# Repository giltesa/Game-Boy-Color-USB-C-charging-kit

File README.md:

# Game Boy Color USB-C Charging Kit

The **Game Boy Color USB-C Charging Kit** is a circuit that allows you to charge a **Nintendo Game Boy Color** by **USB-C** and use a **Li-ion** battery instead of AA batteries.

This circuit includes the famous **TP4056** and **DW01A**. The first one is the device in charge of charging the battery, and the second one is protecting the lifetime of the battery of the over-discharge.

This kit includes two boards. If you want to install it easy, it's enough with the main board which doesn't need any cable for working. However, if you want to have the status LEDs in the same place as the original status LED, then you will need to solder the second board and joint both with 3 cables. You can choose the best option for you.

This is the maind board:

And this one is the LED board:

## Youtube:

Game Boy Color USB-C Charging Kit (Installation)

A small demostration about how this works:

*(red light = charging, green light = finish to charge, white = GBC is power on)*

Battery test: 1500 mAh = 8h 40m

## Would you like it?

https://shop.giltesa.com/product/game-boy-color-usb-c-charging-kit/

## More

- [giltesa.com](https://giltesa.com "giltesa.com")
- [twitter.com](https://twitter.com/giltesa "twitter.com")

## License

This project is licensed under a **Creative Commons** license:
**[Attribution-NonCommercial-ShareAlike 4.0 International (CC BY-NC-SA 4.0) ](https://creativecommons.org/licenses/by-nc-sa/4.0/)**

Check the [LICENSE.md](LICENSE.md) for more information.

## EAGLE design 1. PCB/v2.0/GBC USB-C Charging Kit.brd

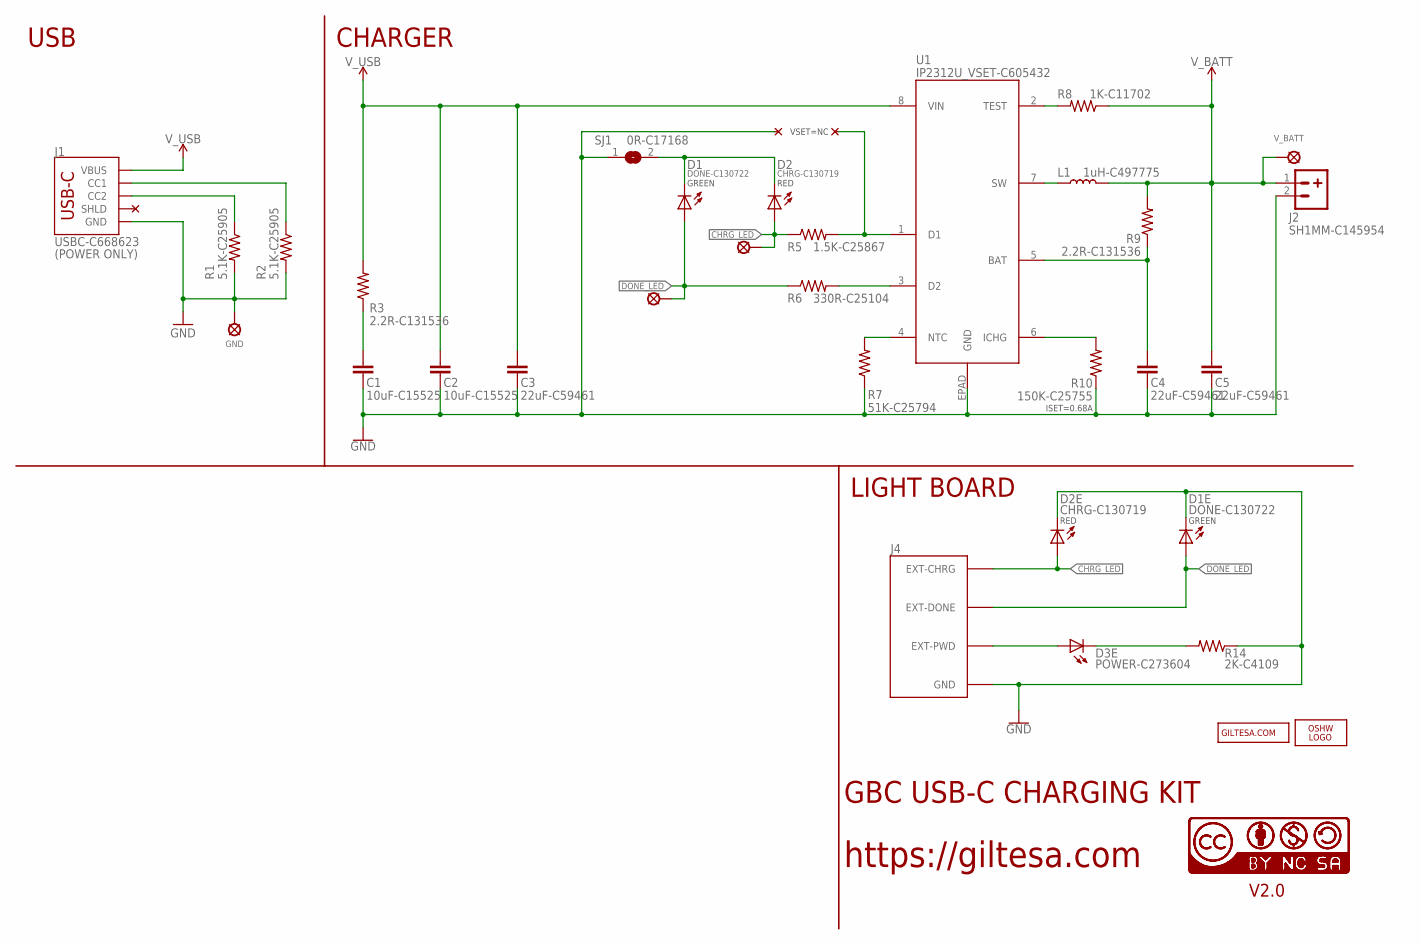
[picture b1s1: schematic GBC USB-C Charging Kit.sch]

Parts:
C1, C2: 10uF-C15525; C0402_S
C3, C4, C5: 22uF-C59461; C0603_S
D1, D1E: DONE-C130722; L0402
D2, D2E: CHRG-C130719; L0402
D3E: POWER-C273604; L0402
J1: USBC-C668623; USB-C_6P
J2: SH1MM-C145954; JST-2-1MM-SMD_RIGHT
J4: GBC_LED_V2
L1: 1uH-C497775; PSPMAA0402
LOGO2: OSHW_LOGO_FILLX0150-NT; OSHW_FILLX150_NOTEXT
R1, R2: 5.1K-C25905; R0402
R3, R9: 2.2R-C131536; R0402
R5: 1.5K-C25867; R0402
R6: 330R-C25104; R0402
R7: 51K-C25794; R0402
R8: 1K-C11702; R0402
R10: 150K-C25755; R0402
R14: 2K-C4109; R0402
SJ1: 0R-C17168; JUMPER-SMD_0402
U1: IP2312U_VSET-C605432; IP2312
U$1: V_BATT; PAD_1.25
U$2: GND; PAD_1.25
U$6: CC-BY-NC-SA15MM; CC-BY-NC-SA_15MM
U$16: GILTESA.COM_MASK; GILTESA.COM_MASK_15MM
U$17: CC-NC-BCNIX; CC-NC-B_NIX
U$24: CHRG_LED; SOLDER_PAD_1.3
U$25: DONE_LED; SOLDER_PAD_1.3

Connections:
CHRG_LED: D2.A, D2E.A, J4.EXT-CHRG, R5.1, U$24.P$1
DONE_LED: D1.A, D1E.A, J4.EXT-DONE, R6.1, U$25.P$1
GND: C1.1, C2.1, C3.1, C4.1, C5.1, D1E.C, D2E.C, J1.A12-GND (GND), J1.B12-GND (GND), J2.2, J4.GND, R1.2, R2.2, R7.1, R10.1, R14.1, SJ1.1, U1.EPAD (GND), U$2.P$1
unnamed: D1.C, D2.C, SJ1.2
unnamed: J1.B5 (CC2), R1.1
unnamed: R8.2, U1.2 (TEST)
unnamed: D3E.A, J4.EXT-PWD
unnamed: D3E.C, R14.2
unnamed: J1.A5 (CC1), R2.1
unnamed: C4.2, R9.1, U1.5 (BAT)
unnamed: C1.2, R3.1
unnamed: R5.2, U1.1 (D1)
unnamed: R7.2, U1.4 (NTC)
unnamed: R10.2, U1.6 (ICHG)
unnamed: R6.2, U1.3 (D2)
unnamed: L1.P$1 (1), U1.7 (SW)
V_BATT: C5.2, J2.1, L1.P$2 (2), R8.1, R9.2, U$1.P$1
V_USB: C2.2, C3.2, J1.A9-VBUS (VBUS), J1.B9-VBUS (VBUS), R3.2, U1.8 (VIN)

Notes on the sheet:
GBC USB-C CHARGING KIT
https://giltesa.com
V2.0
(POWER ONLY)
USB
CHARGER
LIGHT BOARD
ISET=0.68A
GREEN
RED
VSET=NC

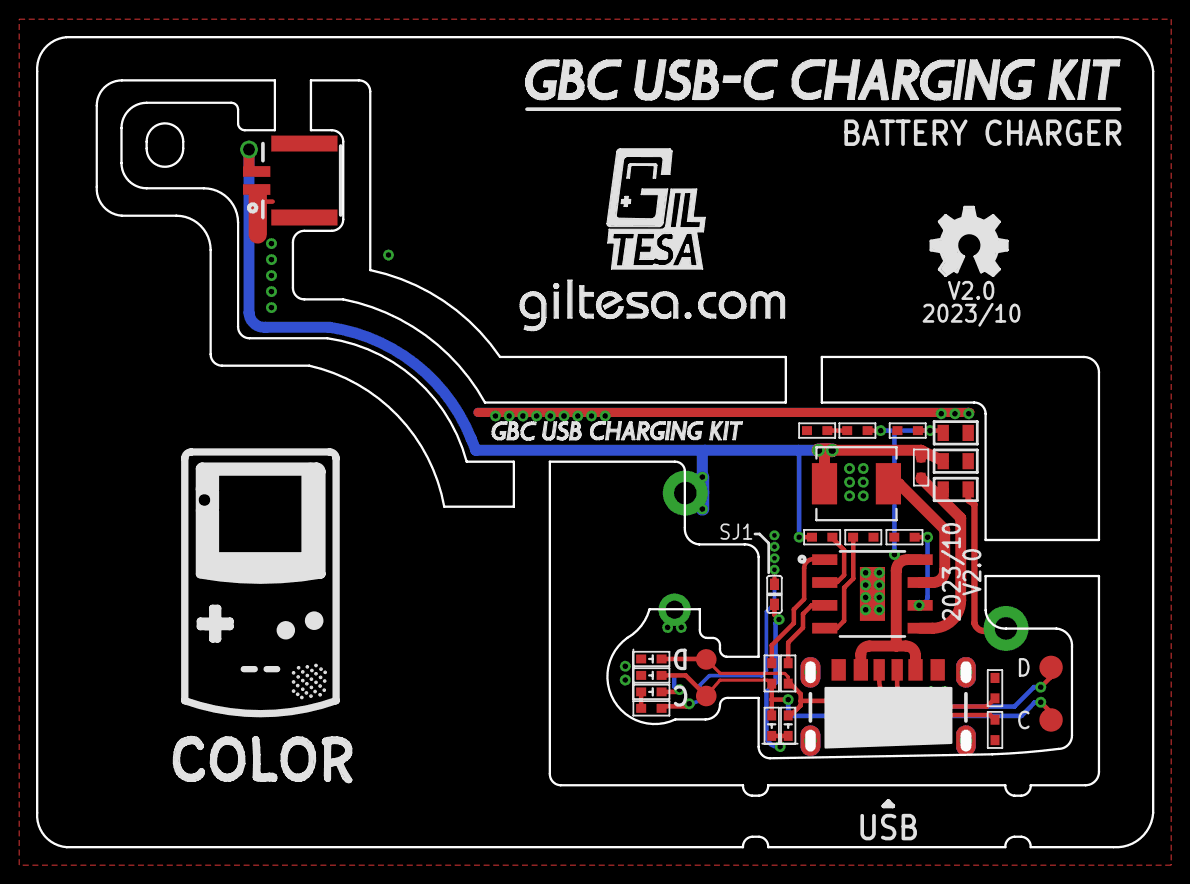
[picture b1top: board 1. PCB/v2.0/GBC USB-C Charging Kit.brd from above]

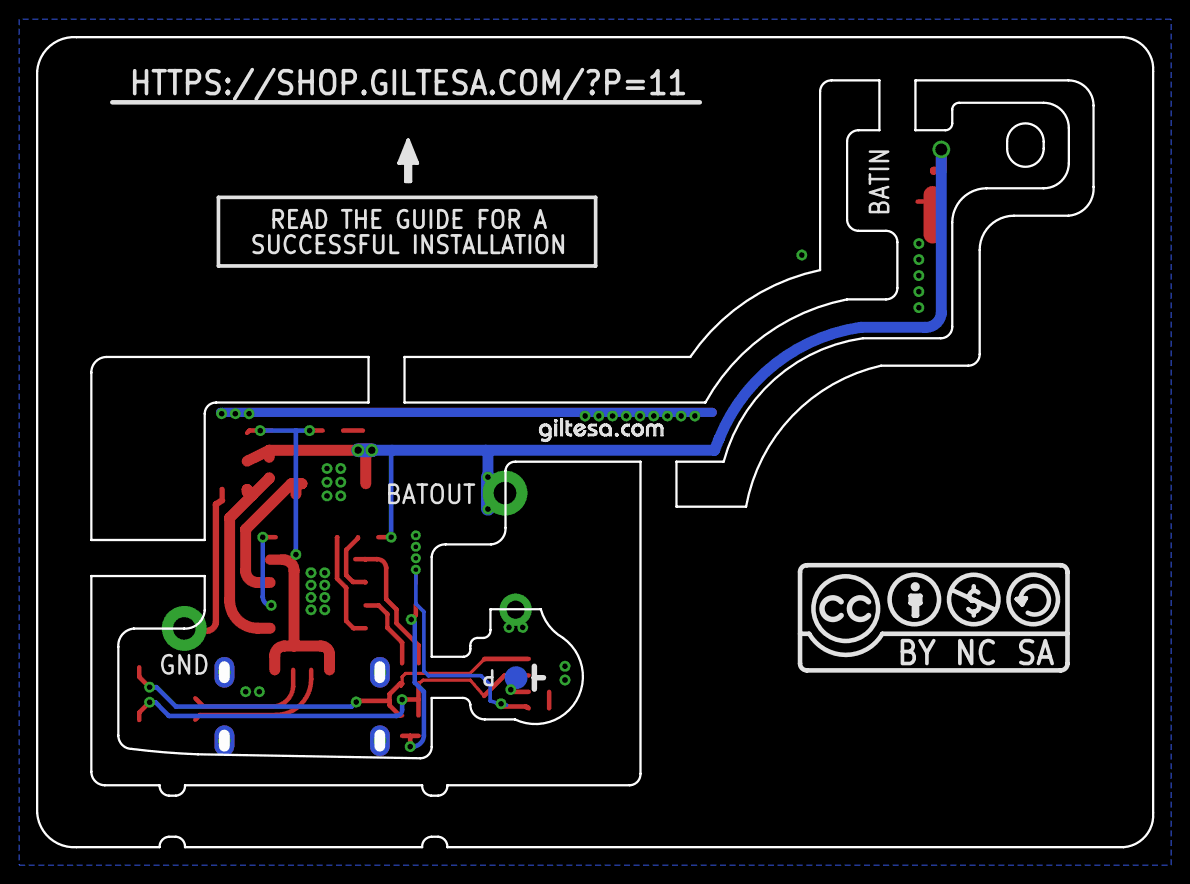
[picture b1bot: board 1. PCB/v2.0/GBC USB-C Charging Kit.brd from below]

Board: 2 copper layers, 62.0 x 45.0 mm, 39 parts (2 on the bottom side), 18 nets.

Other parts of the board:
U$3: GBC_FRAME
U$8: GBC_FRAME_LOGO
U$14: GAME_BOY_COLOR_USB_CHARGING_KIT_NON
U$18: GILTESA_LOGO_MASK_7MM
U$28: GILTESA.COM_MASK_7MM@1

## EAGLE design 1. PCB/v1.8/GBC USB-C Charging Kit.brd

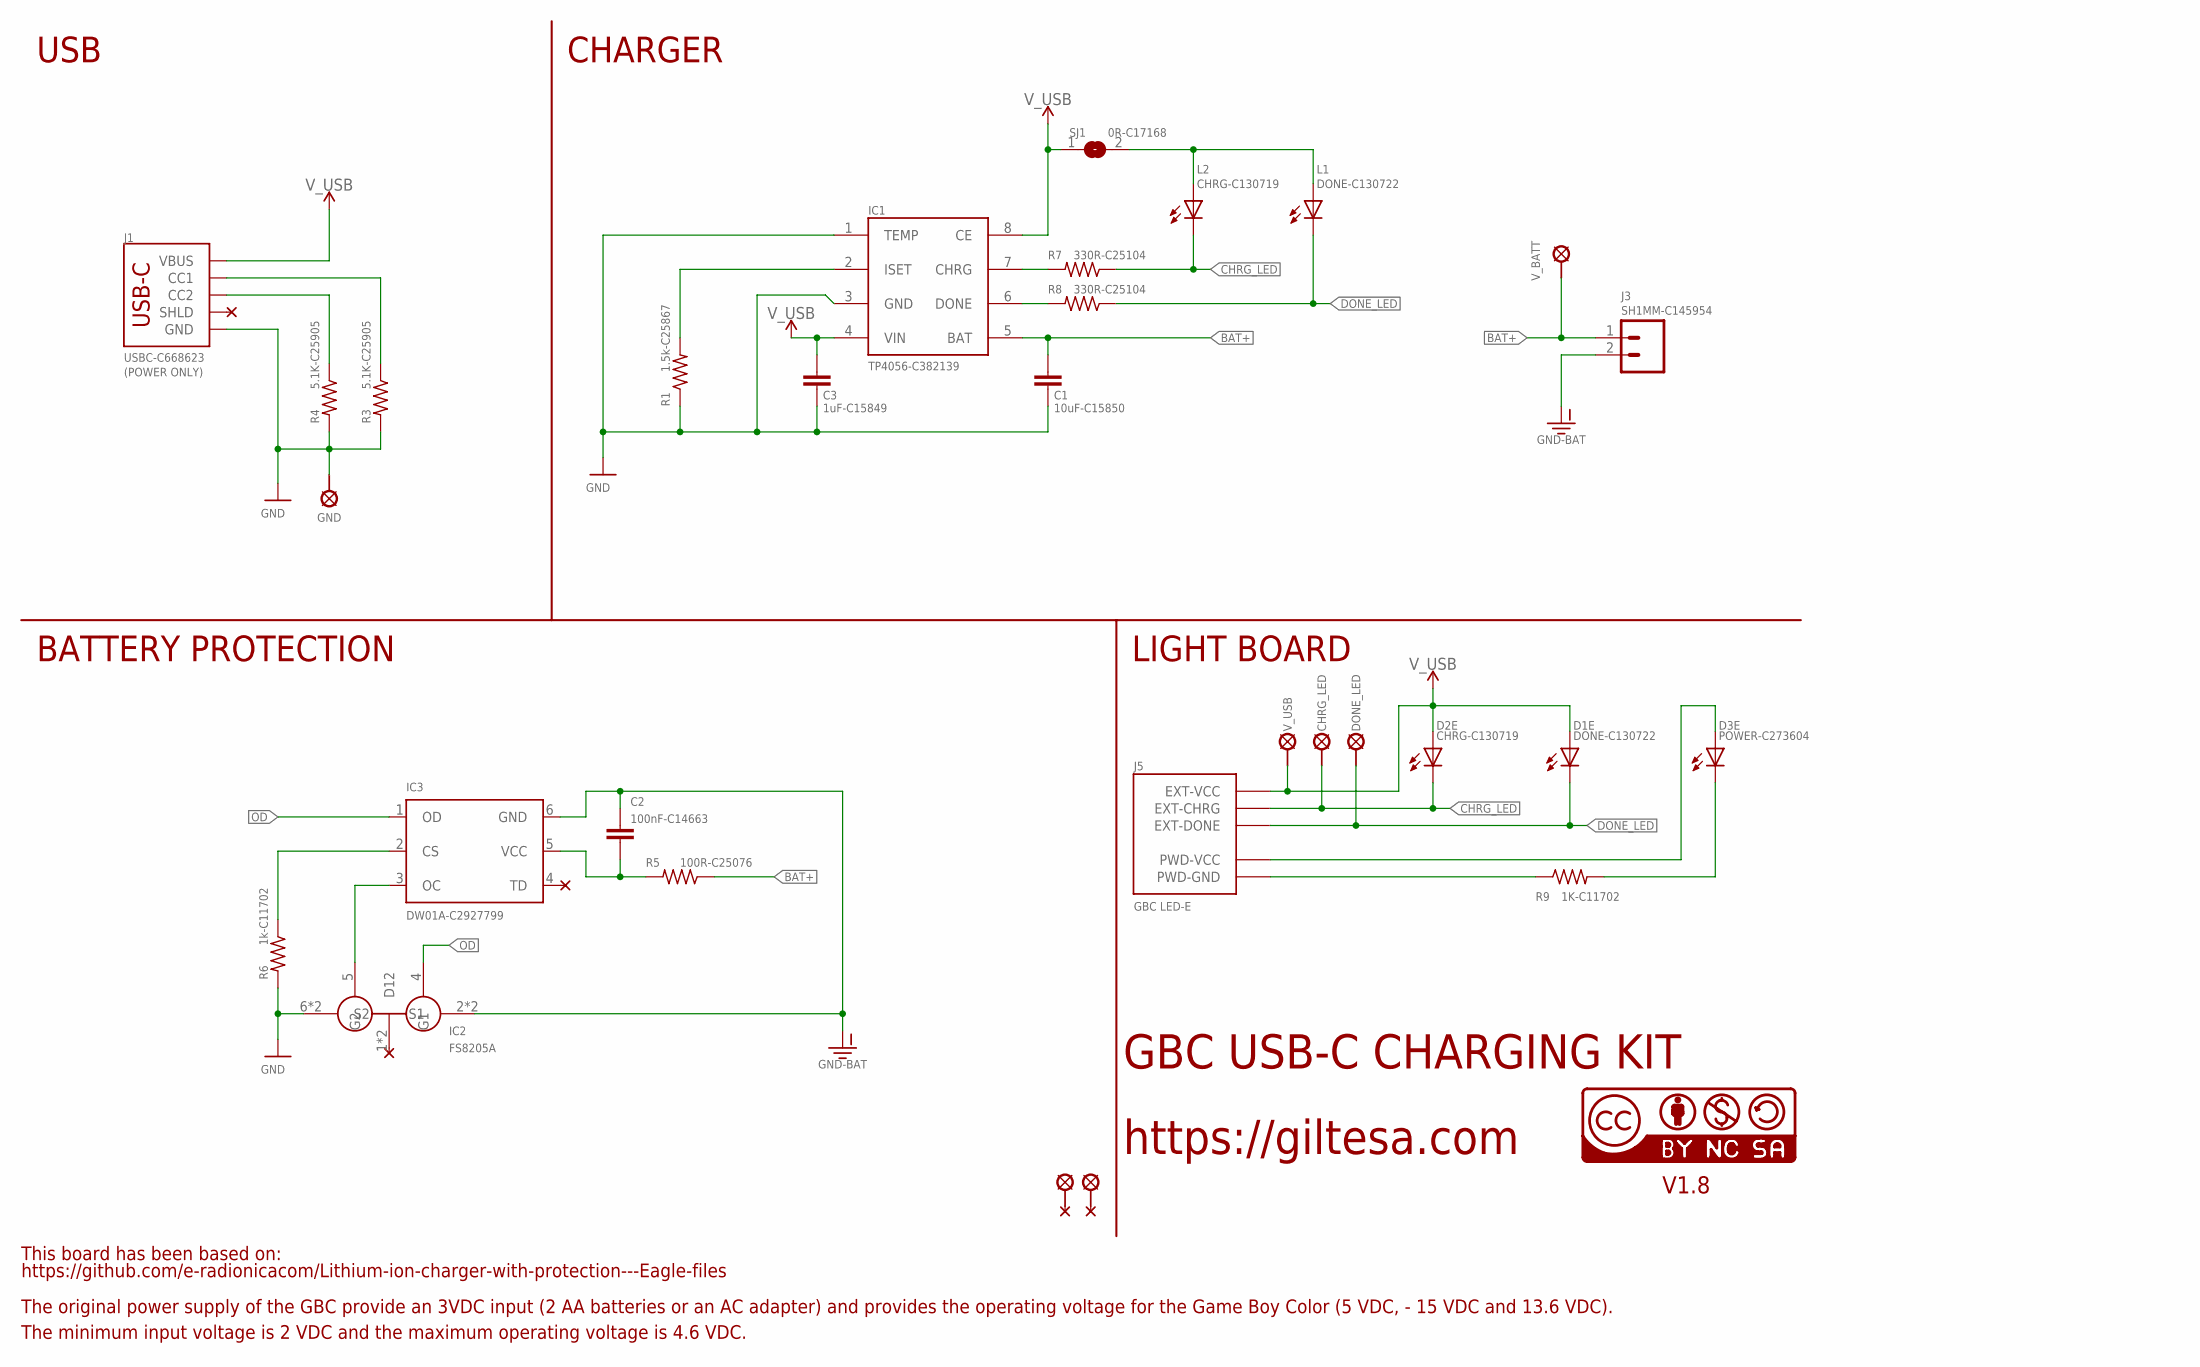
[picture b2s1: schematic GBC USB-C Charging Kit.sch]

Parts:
C1: 10uF-C15850; C0805_S
C2: 100nF-C14663; C0603_S
C3: 1uF-C15849; C0603_S
D1E: DONE-C130722; L0402
D2E: CHRG-C130719; L0402
D3E: POWER-C273604; L0402
IC1: TP4056-C382139; SOIC-8
IC2: 8205A-C2929075; TSSOP8
IC3: DW01A-C2927799; SOT23-6L
J1: USBC-C668623; USB-C_6P
J3: SH1MM-C145954; JST-2-1MM-SMD_RIGHT
J5: GBC LED-E; GBC_LED
L1: DONE-C130722; L0402
L2: CHRG-C130719; L0402
R1: 1.5k-C25867; R0402
R3, R4: 5.1K-C25905; R0402
R5: 100R-C25076; R0402
R6: 1k-C11702; R0402
R7, R8: 330R-C25104; R0402
R9: 1K-C11702; R0402
SJ1: 0R-C17168; JUMPER-SMD_0402
U$2: GND; PAD_1.25
U$17: CC-NC-BCNIX; CC-NC-B_NIX
U$18, U$32: SOLDER_PAD-2.5; SOLDER_PAD_2.5
U$24: CHRG_LED; SOLDER_PAD_1.3
U$25: DONE_LED; SOLDER_PAD_1.3
U$26: V_USB; SOLDER_PAD_1.3
U$29: V_BATT; PAD_1.25

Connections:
BAT+: C1.1, IC1.5 (BAT), J3.1, R5.1, U$29.P$1
CHRG: IC1.7 (CHRG), R7.2
CHRG_LED: D2E.C, J5.EXT-CHRG, L2.C, R7.1, U$24.P$1
DONE: IC1.6 (DONE), R8.2
DONE_LED: D1E.C, J5.EXT-DONE, L1.C, R8.1, U$25.P$1
GND: C1.2, C3.2, IC1.1 (TEMP), IC1.3 (GND), IC2.6 (S2), IC2.7 (S2), J1.GND1 (GND), J1.GND2 (GND), R1.1, R3.2, R4.2, R6.2, U$2.P$1
GND-BAT: C2.1, IC2.2 (S1), IC2.3 (S1), IC3.6 (GND), J3.2
ISET: IC1.2 (ISET), R1.2
unnamed: IC3.2 (CS), R6.1
unnamed: IC2.5 (G2), IC3.3 (OC)
unnamed: L1.A, L2.A, SJ1.2
unnamed: J1.B5 (CC2), R4.1
unnamed: D3E.A, J5.PWD-VCC
unnamed: D3E.C, R9.2
unnamed: J5.PWD-GND, R9.1
unnamed: J1.A5 (CC1), R3.1
OD: IC2.4 (G1), IC3.1 (OD)
VCC-DW: C2.2, IC3.5 (VCC), R5.2
V_USB: C3.1, D1E.A, D2E.A, IC1.4 (VIN), IC1.8 (CE), J1.VBUS1 (VBUS), J1.VBUS2 (VBUS), J5.EXT-VCC, SJ1.1, U$26.P$1

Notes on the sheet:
GBC USB-C CHARGING KIT
https://giltesa.com
V1.8
https://github.com/e-radionicacom/Lithium-ion-charger-with-protection---Eagle-files
This board has been based on:
(POWER ONLY)
IC2
FS8205A
The original power supply of the GBC provide an 3VDC input (2 AA batteries or an AC adapter) and provides the operating voltage for the Game Boy Color (5 VDC, - 15 VDC and 13.6 VDC).
The minimum input voltage is 2 VDC and the maximum operating voltage is 4.6 VDC.
USB
CHARGER
BATTERY PROTECTION
LIGHT BOARD

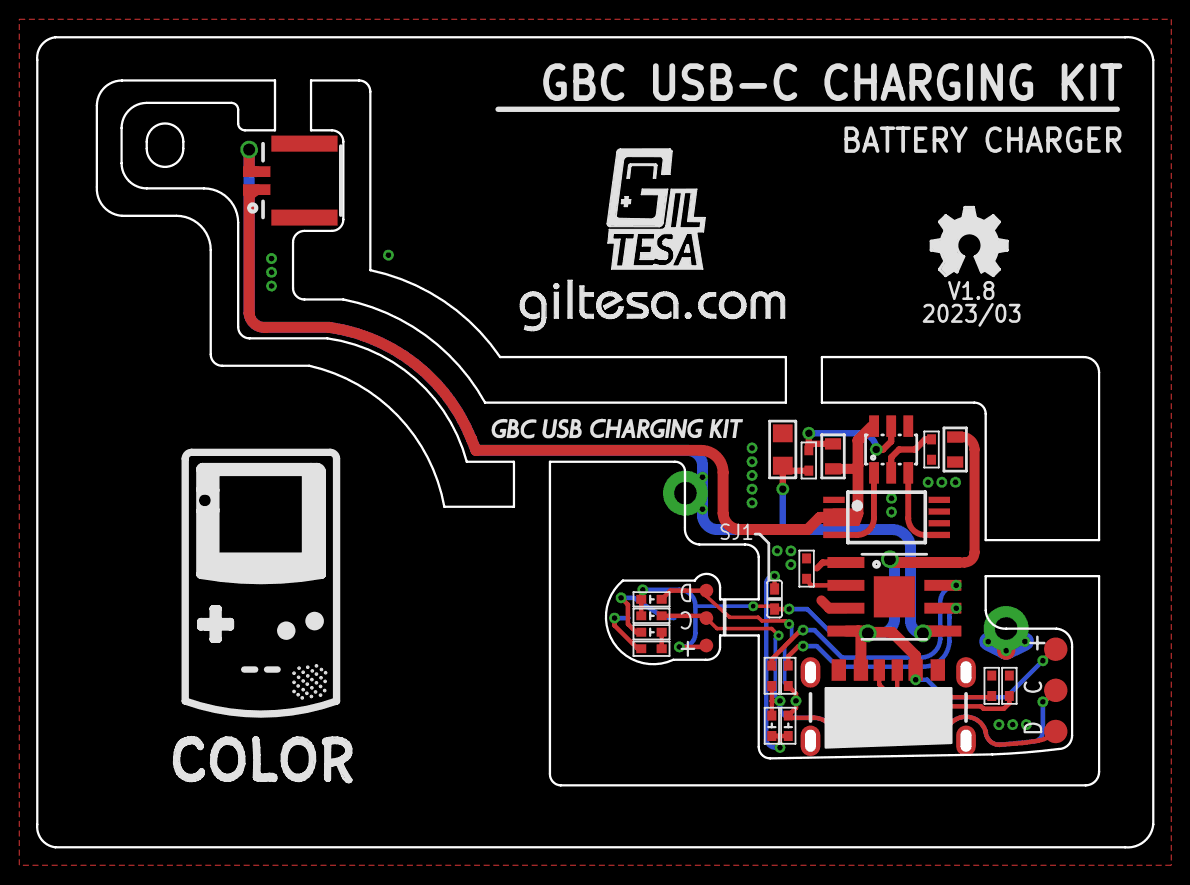
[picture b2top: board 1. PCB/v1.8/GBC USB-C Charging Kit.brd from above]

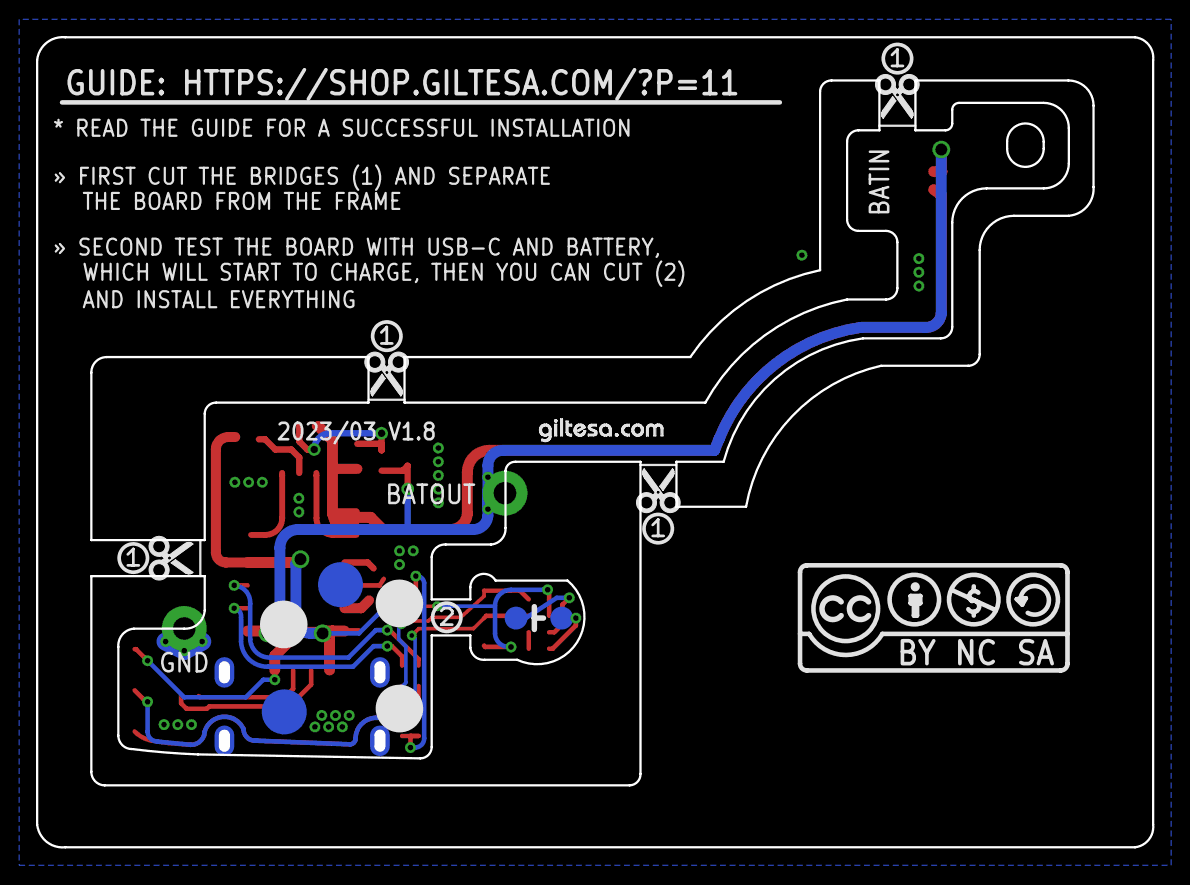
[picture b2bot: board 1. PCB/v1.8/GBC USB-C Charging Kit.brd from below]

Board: 2 copper layers, 62.0 x 45.0 mm, 48 parts (13 on the bottom side), 19 nets.

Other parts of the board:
LOGO3: OSHW_LOGO_FILLX0150-NT; OSHW_FILLX150_NOTEXT
U$4, U$8, U$11, U$13: SCISSOR_ONE
U$6, U$10, U$15, U$27: SCISSOR
U$7: CC-BY-NC-SA15MM; CC-BY-NC-SA_15MM
U$9: GAME_BOY_COLOR_USB_CHARGING_KIT_NON
U$12: GILTESA_LOGO_MASK_7MM
U$14: SCISSOR_TWO
U$20: GILTESA.COM_MASK
U$21: GAME_BOY_COLOR_1.2
U$23: GAME_BOY_COLOR_2
U$28: GILTESA.COM_MASK_7MM

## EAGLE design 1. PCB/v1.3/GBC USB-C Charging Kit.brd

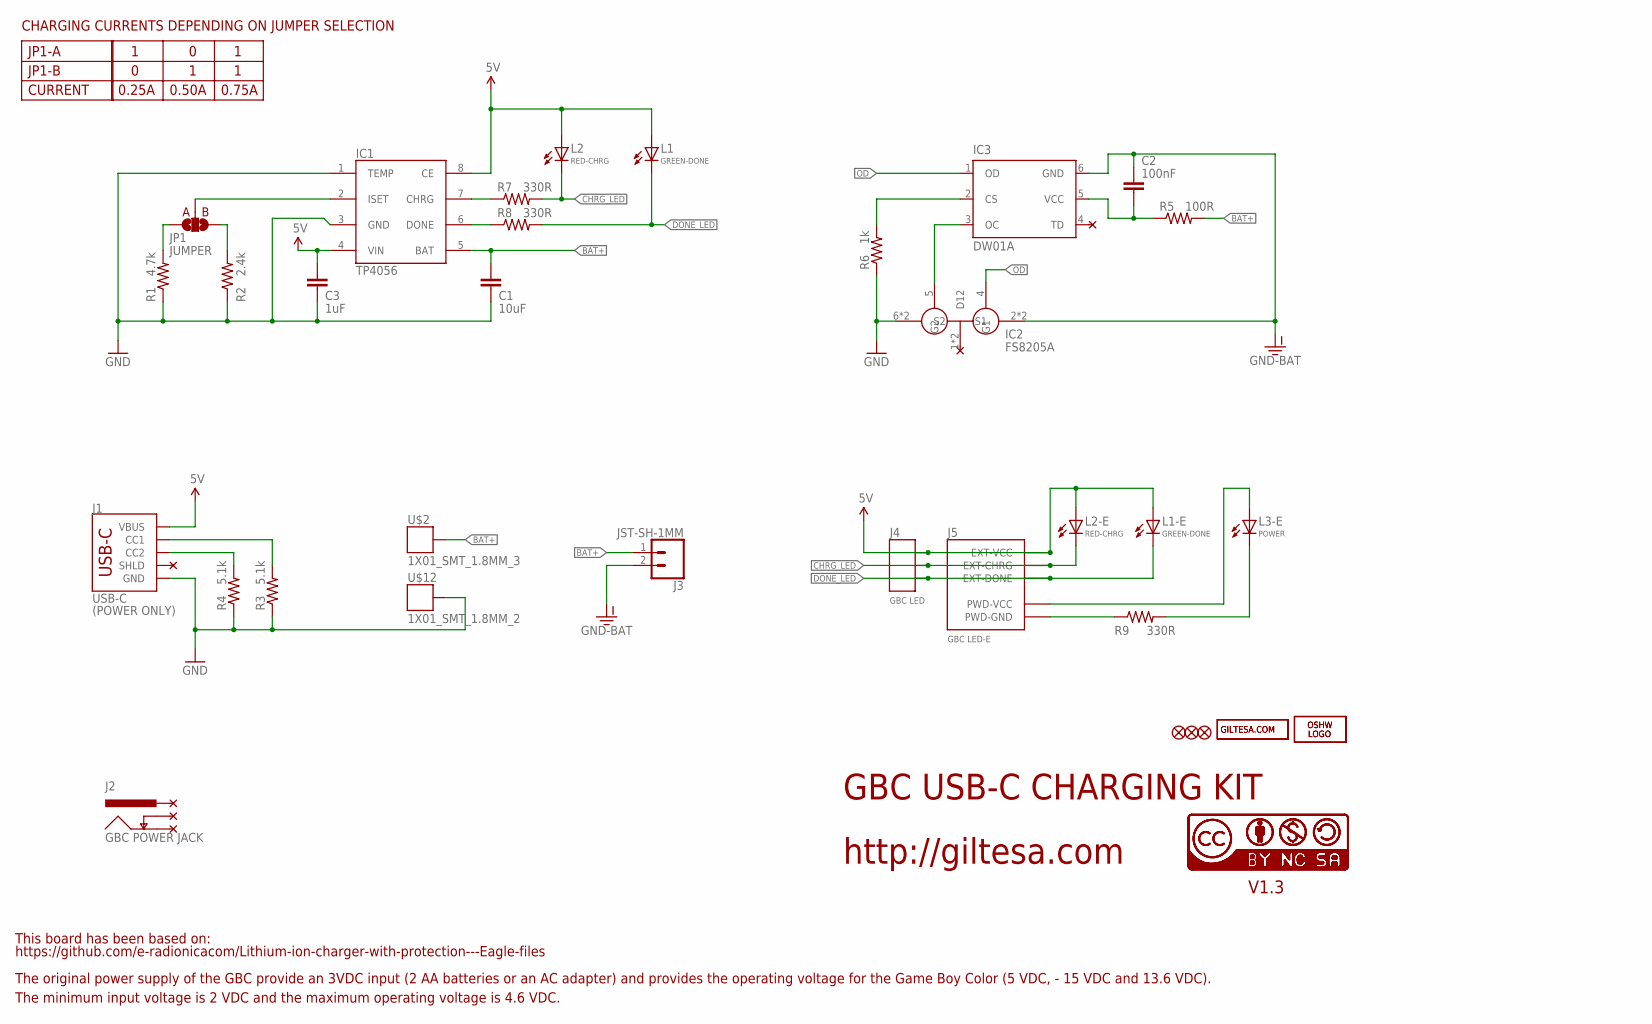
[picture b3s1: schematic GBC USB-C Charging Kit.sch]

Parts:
C1: 10uF; C0805
C2: 100nF; C0603
C3: 1uF; C0603
FD2, FD3, FD4: FIDUCIALUFIDUCIAL; FIDUCIAL-MICRO
IC1: TP4056; SOIC-8
IC2: 8205A; TSSOP8
IC3: DW01A; SOT23-6L
J1: USB-C; USB-C_6P
J2: GBC POWER JACK; GBC_POWER_JACK_2
J3: JST-SH-1MM; JST-2-1MM-SMD_RIGHT
J4: GBC LED; 1X03_SMD_2
J5: GBC LED-E; GBC_LED
JP1: JUMPER; JUMPER-SMD-3_NO_SILK
L1, L1-E: GREEN-DONE; L0402
L2, L2-E: RED-CHRG; L0402
L3-E: POWER; L0402
LOGO1, LOGO2: OSHW_LOGO_FILLX0150-NT; OSHW_FILLX150_NOTEXT
R1: 4.7k; R0402
R2: 2.4k; R0402
R3, R4: 5.1k; R0402
R5: 100R; R0402
R6: 1k; R0402
R7, R8, R9: 330R; R0402
U$2: 1X01_SMT_1.8MM_3
U$6: CC-BY-NC-SA15MM; CC-BY-NC-SA_15MM
U$10, U$16: GILTESA.COM_MASK
U$12: 1X01_SMT_1.8MM_2
U$17: CC-NC-BCNIX; CC-NC-B_NIX

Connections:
5V: C3.1, IC1.4 (VIN), IC1.8 (CE), J1.VBUS1 (VBUS), J1.VBUS2 (VBUS), J4.3, J5.EXT-VCC, L1.A, L1-E.A, L2.A, L2-E.A
BAT+: C1.1, IC1.5 (BAT), J3.1, R5.2, U$2.P$1
CHRG: IC1.7 (CHRG), R7.1
CHRG_LED: J4.2, J5.EXT-CHRG, L2.C, L2-E.C, R7.2
DONE: IC1.6 (DONE), R8.1
DONE_LED: J4.1, J5.EXT-DONE, L1.C, L1-E.C, R8.2
GND: C1.2, C3.2, IC1.1 (TEMP), IC1.3 (GND), IC2.6 (S2), IC2.7 (S2), J1.GND1 (GND), J1.GND2 (GND), R1.1, R2.1, R3.1, R4.1, R6.1, U$12.P$1
GND-BAT: C2.1, IC2.2 (S1), IC2.3 (S1), IC3.6 (GND), J3.2
ISET: IC1.2 (ISET), JP1.2
unnamed: IC3.2 (CS), R6.2
unnamed: IC2.5 (G2), IC3.3 (OC)
unnamed: J1.B5 (CC2), R4.2
unnamed: JP1.3, R2.2
unnamed: JP1.1, R1.2
unnamed: J5.PWD-VCC, L3-E.A
unnamed: L3-E.C, R9.2
unnamed: J5.PWD-GND, R9.1
unnamed: J1.A5 (CC1), R3.2
OD: IC2.4 (G1), IC3.1 (OD)
VCC-DW: C2.2, IC3.5 (VCC), R5.1

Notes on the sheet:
GBC USB-C CHARGING KIT
http://giltesa.com
V1.3
JP1-A
JP1-B
CURRENT
0.25A
0.50A
0.75A
CHARGING CURRENTS DEPENDING ON JUMPER SELECTION
https://github.com/e-radionicacom/Lithium-ion-charger-with-protection---Eagle-files
This board has been based on:
(POWER ONLY)
IC2
FS8205A
The original power supply of the GBC provide an 3VDC input (2 AA batteries or an AC adapter) and provides the operating voltage for the Game Boy Color (5 VDC, - 15 VDC and 13.6 VDC).
The minimum input voltage is 2 VDC and the maximum operating voltage is 4.6 VDC.

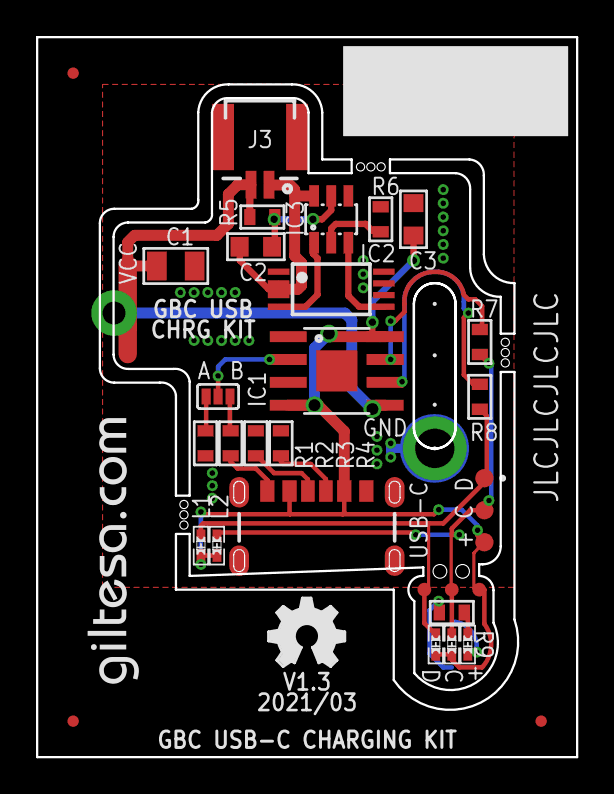
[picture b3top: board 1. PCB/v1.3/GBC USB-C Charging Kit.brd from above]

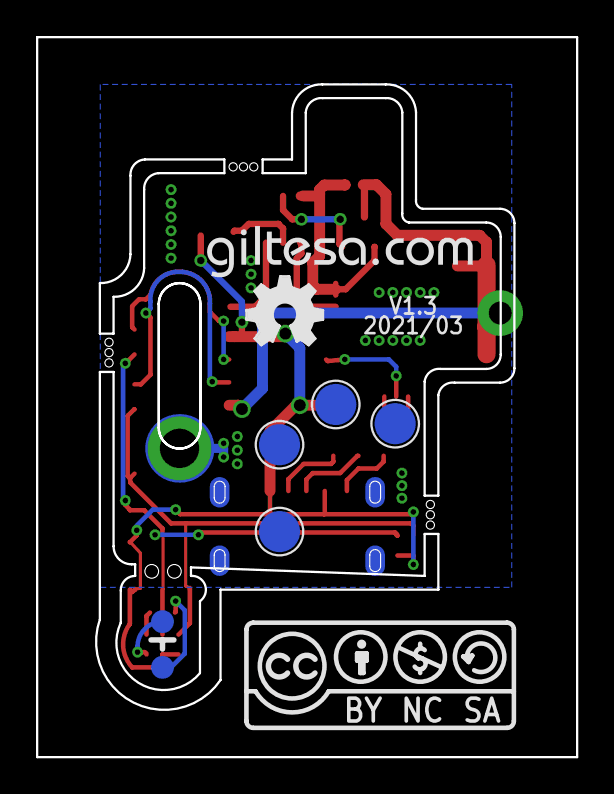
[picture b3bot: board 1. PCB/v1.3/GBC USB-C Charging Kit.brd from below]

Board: 2 copper layers, 30.0 x 40.0 mm, 37 parts (3 on the bottom side), 20 nets.

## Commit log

2021-01-14 v1.2
2021-01-16 Added “R” to any resistance with a value less than 1K
2021-01-20 no message
2021-02-01 Ordening the repo.
2021-02-19 Added info about how to check the white LED on the LED board.
2021-03-03 Added battery info.
2021-03-06 Added Battery test: 1500 mAh = 8h 40m
2021-04-10 v1.3
2023-01-28 Updated the guide
2023-08-14 v1.8
2023-10-29 v2.0

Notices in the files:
parts and their libraries:
SparkFun: Licensing: CC v3.0 Share-Alike You are welcome to use this library for commercial purposes.
SparkFun-Jumpers: Licensing: Creative Commons ShareAlike 4.0 International - https://creativecommons.org/licenses/by-sa/4.0
cc-by-nc-sa: All hardware is licensed under the Creative Commons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
